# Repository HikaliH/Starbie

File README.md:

It's a little totoro (character from My Neighbor Totoro) shaped tamagotchi basically! Make your own with this guide: https://github.com/SharKingStudios/Starbie/blob/main/Week%201%20Guide.md

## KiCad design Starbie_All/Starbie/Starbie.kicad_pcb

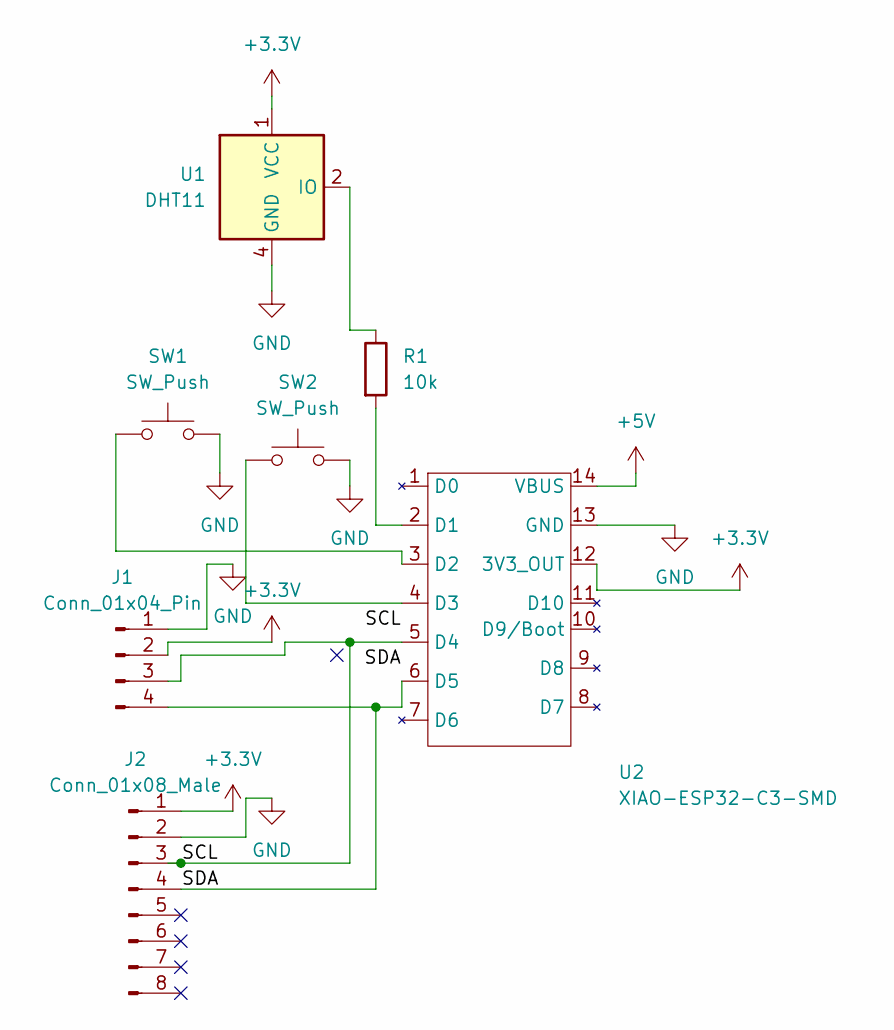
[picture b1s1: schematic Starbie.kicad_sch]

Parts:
J1: Conn_01x04_Pin; PinSocket_1x04_P2.54mm_Vertical
J2: Conn_01x08_Male; PinHeader_1x08_P2.54mm_Vertical
R1: 10k; R_Axial_DIN0204_L3.6mm_D1.6mm_P7.62mm_Horizontal
SW1, SW2: SW_Push; SW_Cherry_MX_1.00u_PCB
U1: DHT11; Aosong_DHT11_5.5x12.0_P2.54mm
U2: XIAO-ESP32-C3-SMD; XIAO-ESP32-C6-DIP

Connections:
+3.3V: J1.2, J2.1, U1.1 (VCC), U2.12 (3V3_OUT)
+5V: U2.14 (VBUS)
/SCL: J1.3, J2.3, U2.5 (D4)
/SDA: J1.4, J2.4, U2.6 (D5)
GND: J1.1, J2.2, SW1.2, SW2.2, U1.4 (GND), U2.13 (GND)
unnamed: R1.1, U1.2 (IO)
unnamed: R1.2, U2.2 (D1)
unnamed: SW1.1, U2.3 (D2)
unnamed: SW2.1, U2.4 (D3)

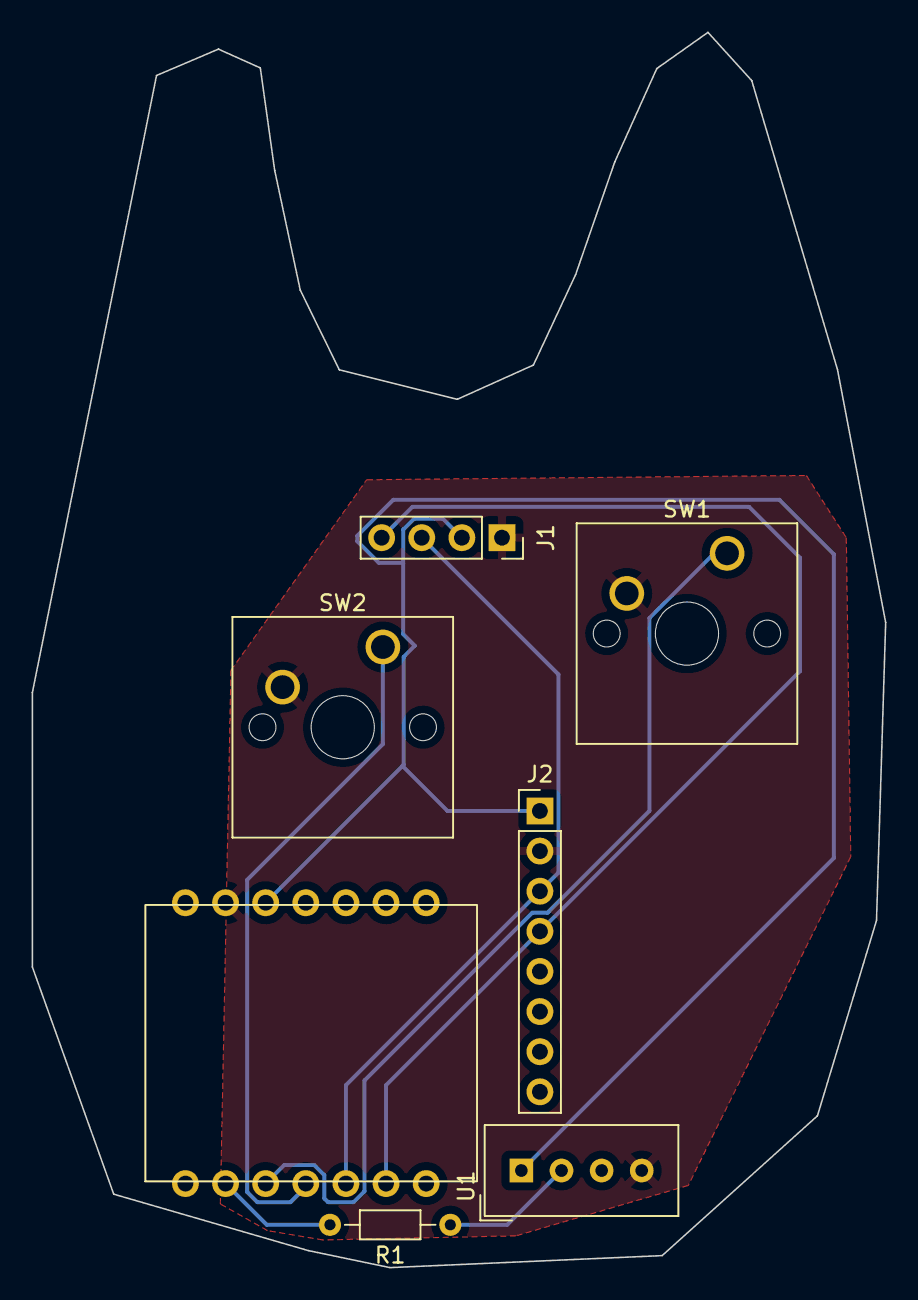
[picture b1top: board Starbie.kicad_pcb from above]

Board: 2 copper layers, 54.0 x 78.2 mm, 7 parts (0 on the bottom side), 8 nets.
